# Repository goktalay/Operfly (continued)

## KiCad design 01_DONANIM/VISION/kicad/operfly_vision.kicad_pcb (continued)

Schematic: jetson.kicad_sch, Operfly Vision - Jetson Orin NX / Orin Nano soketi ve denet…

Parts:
C51: 1n; C_0402_1005Metric
C52, C53, C54, C55, C56, C57, C58, C59, C60, C61, C62, C63: 220n; C_0402_1005Metric
J2: Jetson Orin NX / Orin Nano; SODIMM-260_DDR4_H4.0-5.2_OrientationStd_Socket
Q2, Q3: 2N7002; SOT-23
R41: 1k; R_0402_1005Metric
R42, R45, R46, R47: 100k; R_0402_1005Metric
R43: 100k 1%; R_0402_1005Metric
R44: 33k 1%; R_0402_1005Metric
R48, R49: 0R; R_0402_1005Metric
TP7: JET_SYS_RESET_N; TestPoint_Pad_D1.0mm
TP8: JET_FRC_N; TestPoint_Pad_D1.0mm
TP9: JET_MOD_SLEEP_N; TestPoint_Pad_D1.0mm
TP10: JET_SLEEP_WAKE_N; TestPoint_Pad_D1.0mm
TP11: JET_DBG_TX; TestPoint_Pad_D1.0mm
TP12: JET_DBG_RX; TestPoint_Pad_D1.0mm

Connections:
+3V3: R45.1; also elsewhere on the board
+12V_JET: J2.251 (VDD_IN), J2.252 (VDD_IN), J2.253 (VDD_IN), J2.254 (VDD_IN), J2.255 (VDD_IN), J2.256 (VDD_IN), J2.257 (VDD_IN), J2.258 (VDD_IN), J2.259 (VDD_IN), J2.260 (VDD_IN); also elsewhere on the board
E1_CLKREQ_N: J2.182 (PCIE1_CLKREQ*), R48.1
E1_CLK_N: J2.173 (PCIE1_CLK_N); also elsewhere on the board
E1_CLK_P: J2.175 (PCIE1_CLK_P); also elsewhere on the board
E1_PER_N: C61.2; also elsewhere on the board
E1_PER_P: C60.2; also elsewhere on the board
E1_PET_C_N: J2.167 (PCIE1_RX0_N); also elsewhere on the board
E1_PET_C_P: J2.169 (PCIE1_RX0_P); also elsewhere on the board
E1_RST_N: J2.183 (PCIE1_RST*); also elsewhere on the board
E2_CLKREQ_N: J2.221 (PCIE2_CLKREQ*), R49.1
E2_CLK_N: J2.52 (PCIE2_CLK_N); also elsewhere on the board
E2_CLK_P: J2.54 (PCIE2_CLK_P); also elsewhere on the board
E2_PER_N: C63.2; also elsewhere on the board
E2_PER_P: C62.2; also elsewhere on the board
E2_PET_C_N: J2.40 (PCIE2_RX0_N); also elsewhere on the board
E2_PET_C_P: J2.42 (PCIE2_RX0_P); also elsewhere on the board
E2_RST_N: J2.219 (PCIE2_RST*); also elsewhere on the board
GND: C51.2, J2.1 (GND), J2.2 (GND), J2.7 (GND), J2.8 (GND), J2.13 (GND), J2.14 (GND), J2.19 (GND), J2.20 (GND), J2.25 (GND), J2.26 (GND), J2.31 (GND), J2.32 (GND), J2.37 (GND), J2.38 (GND), J2.43 (GND), J2.44 (GND), J2.49 (GND), J2.50 (GND), J2.55 (GND), J2.56 (GND), J2.61 (GND), J2.62 (GND), J2.67 (GND), J2.68 (GND), J2.73 (GND), J2.74 (GND), J2.79 (GND), J2.80 (GND), J2.85 (GND), J2.86 (GND), J2.102 (GND), J2.107 (GND), J2.113 (GND), J2.119 (GND), J2.125 (GND), J2.129 (GND), J2.132 (GND), J2.135 (GND), J2.138 (GND), J2.141 (GND), J2.144 (GND), J2.146 (GND), J2.147 (GND), J2.152 (GND), J2.153 (GND), J2.158 (GND), J2.159 (GND), J2.164 (GND), J2.165 (GND), J2.170 (GND), J2.171 (GND), J2.176 (GND), J2.177 (GND), J2.200 (GND), J2.201 (GND), J2.231 (GND), J2.241 (GND), J2.242 (GND), J2.243 (GND), J2.244 (GND), J2.245 (GND), J2.246 (GND), J2.247 (GND), J2.248 (GND), J2.249 (GND), J2.250 (GND), Q2.2 (S), Q3.2 (S), R42.2, R44.2, R46.2, R47.2, R48.2, R49.2; also elsewhere on the board
IMU_CS_N: J2.95 (SPI0_CS0*); also elsewhere on the board
IMU_INT: J2.211 (GPIO09); also elsewhere on the board
IMU_MISO: J2.93 (SPI0_MISO); also elsewhere on the board
IMU_MOSI: J2.89 (SPI0_MOSI); also elsewhere on the board
IMU_SCK: J2.91 (SPI0_SCK); also elsewhere on the board
JET_DBG_RX: J2.238 (UART2_RXD), TP12.1
JET_DBG_TX: J2.236 (UART2_TXD), TP11.1
JET_FAN_PWM_1V8: J2.230 (GPIO14); also elsewhere on the board
JET_FRC_N: J2.214 (FORCE_RECOVERY*), Q3.3 (D), TP8.1
JET_MODULE_ID: J2.217 (MODULE_ID), R45.2; also elsewhere on the board
JET_MOD_SLEEP_N: J2.178 (MOD_SLEEP*), TP9.1
JET_POWER_EN: R41.1, R42.1; also elsewhere on the board
JET_POWER_EN_R: J2.237 (POWER_EN), R41.2
JET_PPS_1V8: J2.206 (GPIO07); also elsewhere on the board
JET_RECOVERY: Q3.1 (G), R47.1; also elsewhere on the board
JET_RESET: Q2.1 (G), R46.1; also elsewhere on the board
JET_SHDN_REQ_12V: J2.233 (SHUTDOWN_REQ*), R43.1
JET_SHDN_REQ_N: C51.1, R43.2, R44.1; also elsewhere on the board
JET_SLEEP_WAKE_N: J2.240 (SLEEP/WAKE*), TP10.1
JET_SYS_RESET_N: J2.239 (SYS_RESET*), Q2.3 (D), TP7.1; also elsewhere on the board
JET_UART_RX_1V8: J2.205 (UART1_RXD); also elsewhere on the board
JET_UART_TX_1V8: J2.203 (UART1_TXD); also elsewhere on the board
JGBE_MDI0_N: J2.184 (GBE_MDI0_N); also elsewhere on the board
JGBE_MDI0_P: J2.186 (GBE_MDI0_P); also elsewhere on the board
JGBE_MDI1_N: J2.190 (GBE_MDI1_N); also elsewhere on the board
JGBE_MDI1_P: J2.192 (GBE_MDI1_P); also elsewhere on the board
JGBE_MDI2_N: J2.196 (GBE_MDI2_N); also elsewhere on the board
JGBE_MDI2_P: J2.198 (GBE_MDI2_P); also elsewhere on the board
JGBE_MDI3_N: J2.202 (GBE_MDI3_N); also elsewhere on the board
JGBE_MDI3_P: J2.204 (GBE_MDI3_P); also elsewhere on the board
J_PCIE0_TX0_N: C53.1, J2.134 (PCIE0_TX0_N)
J_PCIE0_TX0_P: C52.1, J2.136 (PCIE0_TX0_P)
J_PCIE0_TX1_N: C55.1, J2.140 (PCIE0_TX1_N)
J_PCIE0_TX1_P: C54.1, J2.142 (PCIE0_TX1_P)
J_PCIE0_TX2_N: C57.1, J2.148 (PCIE0_TX2_N)
J_PCIE0_TX2_P: C56.1, J2.150 (PCIE0_TX2_P)
J_PCIE0_TX3_N: C59.1, J2.154 (PCIE0_TX3_N)
J_PCIE0_TX3_P: C58.1, J2.156 (PCIE0_TX3_P)
J_PCIE1_TX_N: C61.1, J2.172 (PCIE1_TX0_N)
J_PCIE1_TX_P: C60.1, J2.174 (PCIE1_TX0_P)
J_PCIE2_TX_N: C63.1, J2.46 (PCIE2_TX0_N)
J_PCIE2_TX_P: C62.1, J2.48 (PCIE2_TX0_P)
M2_CLKREQ_N: J2.180 (PCIE0_CLKREQ*); also elsewhere on the board
M2_CLK_N: J2.160 (PCIE0_CLK_N); also elsewhere on the board
M2_CLK_P: J2.162 (PCIE0_CLK_P); also elsewhere on the board
M2_PER0_N: J2.131 (PCIE0_RX0_N); also elsewhere on the board
M2_PER0_P: J2.133 (PCIE0_RX0_P); also elsewhere on the board
M2_PER1_N: J2.137 (PCIE0_RX1_N); also elsewhere on the board
M2_PER1_P: J2.139 (PCIE0_RX1_P); also elsewhere on the board
M2_PER2_N: J2.149 (PCIE0_RX2_N); also elsewhere on the board
M2_PER2_P: J2.151 (PCIE0_RX2_P); also elsewhere on the board
M2_PER3_N: J2.155 (PCIE0_RX3_N); also elsewhere on the board
M2_PER3_P: J2.157 (PCIE0_RX3_P); also elsewhere on the board
M2_PET0_N: C53.2; also elsewhere on the board
M2_PET0_P: C52.2; also elsewhere on the board
M2_PET1_N: C55.2; also elsewhere on the board
M2_PET1_P: C54.2; also elsewhere on the board
M2_PET2_N: C57.2; also elsewhere on the board
M2_PET2_P: C56.2; also elsewhere on the board
M2_PET3_N: C59.2; also elsewhere on the board
M2_PET3_P: C58.2; also elsewhere on the board
M2_RST_N: J2.181 (PCIE0_RST*); also elsewhere on the board
PCIE_WAKE_N: J2.179 (PCIE_WAKE*); also elsewhere on the board
USB0_DM: J2.109 (USB0_D_N); also elsewhere on the board
USB0_DP: J2.111 (USB0_D_P); also elsewhere on the board
USB0_VBUS_DET_N: J2.87 (GPIO00); also elsewhere on the board

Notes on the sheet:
MODULE_ID: Orin'de bosta (100k ile 3,3 V'a cekilir = 1), yalniz 5 V'luk eski modulde GND.
Uc tablosu uretici veri sayfasindan (10_ORTAK_ARACLAR/kicad/jetson_uclari.py). Bos birakilan uclar bu kartta kullanilmaz.
JETSON SOKETI (260 uclu SO-DIMM). Birimler: guc ve denetim | PCIe, Ethernet, USB | dusuk hizli giris-cikislar | kullanilmayan goruntu uclari.
DENETIM: POWER_EN islemciden (1k seri; modulde 100k asagi cekme). SHUTDOWN_REQ* modulde 5k ile 12 V'a cekilidir -> 100k/33k ile islemciye.
PCIe: Jetson'in verici ciftlerinde 220 nF (alicilarin kondansatoru karsi taraftadir). Ethernet denetleyicilerinde saat istegi ucu yok:
SYS_RESET* ve FORCE_RECOVERY* 1,8 V hatlardir: islemci yalnizca transistorle DUSUGE ceker, hicbir zaman yuksege surmez.
PCIE1/PCIE2 CLKREQ* 0R ile GND'ye (saat surekli). Kondansatorler Jetson soketinin yanina konur.

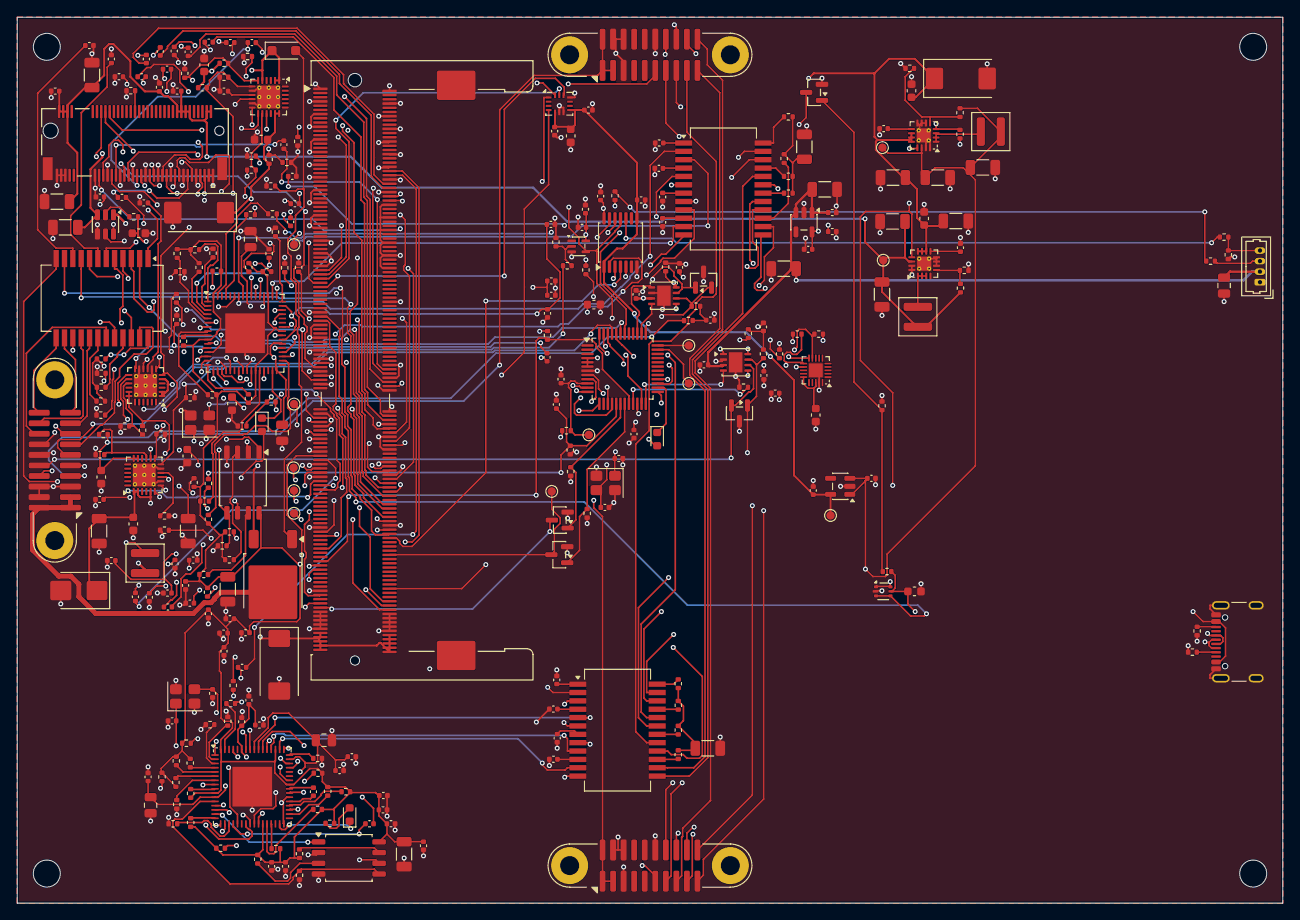
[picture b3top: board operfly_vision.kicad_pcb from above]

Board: 6 copper layers, 150.0 x 105.0 mm, 312 parts (0 on the bottom side), 300 nets.

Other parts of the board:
H1, H2, H3, H4: M3; MountingHole_3.2mm_M3

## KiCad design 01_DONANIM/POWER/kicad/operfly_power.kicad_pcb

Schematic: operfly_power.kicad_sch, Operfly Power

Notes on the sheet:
Operfly Power - guc karti (OPFPWR)
Sematik betikle uretilir: 01_DONANIM/POWER/kicad/uret.py.

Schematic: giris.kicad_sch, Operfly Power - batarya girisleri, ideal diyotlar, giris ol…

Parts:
C24, C26: 47n 100V; C_0603_1608Metric
C25, C27, C28, C29: 100n; C_0402_1005Metric
C30, C31: 100u 80V; CP_Elec_10x10.5
C32, C33: 2u2 100V; C_1210_3225Metric
D6, D8: SMAT70A; D_SMA
D7, D9: SMAJ24A; D_SMA
J2: Batarya A (XT60); AMASS_XT60-M_1x02_P7.20mm_Vertical
J3: Batarya B (XT60); AMASS_XT60-M_1x02_P7.20mm_Vertical
Q1, Q2: 100V lojik seviye, <=4 mR (secilecek); TDSON-8-1
R13, R16: 1k; R_0402_1005Metric
R14, R17: 200k 1%; R_0402_1005Metric
R15, R18: 10k 1%; R_0402_1005Metric
R19: 0R0005 1% 3W; R_Shunt_Isabellenhuette_BVR4026
R20, R21: 10R; R_0402_1005Metric
R22, R23: 2k2; R_0402_1005Metric
R24: 10k; R_0402_1005Metric
TP4: VIN; TestPoint_Pad_D1.0mm
U7, U8: LTC4359IDCB; DFN-6-1EP_3x2mm_P0.5mm_EP1.65x1.35mm
U9: INA228AIDGSR; TSSOP-10_3x3mm_P0.5mm

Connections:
+3V3: C29.1, R22.1, R23.1, R24.1, U9.6 (VS); also elsewhere on the board
BAT_A: D6.1 (K), J2.1, Q1.1 (S), Q1.2 (S), Q1.3 (S), R14.1, U7.3 (SRC), U7.4 (IN)
BAT_B: D8.1 (K), J3.1, Q2.1 (S), Q2.2 (S), Q2.3 (S), R17.1, U8.3 (SRC), U8.4 (IN)
GATE_A: Q1.4 (G), U7.2 (GATE)
GATE_B: Q2.4 (G), U8.2 (GATE)
GND: C24.2, C25.2, C26.2, C27.2, C29.2, C30.2, C31.2, C32.2, C33.2, D7.1 (K), D9.1 (K), J2.2, J3.2, R13.2, R15.2, R16.2, R18.2, U9.1 (A1), U9.2 (A0), U9.7 (GND); also elsewhere on the board
INA_INN: C28.2, R21.2, U9.9 (Vin-)
INA_INP: C28.1, R20.2, U9.10 (Vin+)
PWR_ALERT_N: R24.2, U9.3 (~Alert); also elsewhere on the board
PWR_SCL: R22.2, U9.5 (SCL); also elsewhere on the board
PWR_SDA: R23.2, U9.4 (SDA); also elsewhere on the board
SHUNT_N: R19.3, R21.1
SHUNT_P: R19.2, R20.1
TVS_A: D6.2 (A), D7.2 (A)
TVS_B: D8.2 (A), D9.2 (A)
VBAT_A_SENS: C25.1, R14.2, R15.1; also elsewhere on the board
VBAT_B_SENS: C27.1, R17.2, R18.1; also elsewhere on the board
VIN: C30.1, C31.1, C32.1, C33.1, R19.4, TP4.1, U9.8 (Vbus); also elsewhere on the board
VIN_OR: C24.1, C26.1, Q1.5 (D), Q2.5 (D), R19.1, U7.1 (OUT), U8.1 (OUT)
VSS_A: R13.1, U7.6 (Vss), U7.7 (Pad)
VSS_B: R16.1, U8.6 (Vss), U8.7 (Pad)

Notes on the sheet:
GIRIS OLCUMU (INA228): gerilim, akim ve harcanan enerji; I2C ile dugum islemcisine. Akim direnci 0,5 mR (30 A'de 0,45 W).
giriste iki kirpma diyotu (70 V ve ters yonde 24 V), VSS ucunda 1 k, cikista 47 nF. Ters baglanan batarya -40 V'a kadar zarar vermez.
BATARYA GIRISLERI (6-60 V): her giriste ideal diyot (LTC4359 + N kanal MOSFET). Devre ureticinin ornek devresidir:
VIN: olculmus, birlestirilmis giris gerilimi; 12 V ceviriciye ve servo rayina gider (bu sayfalar henuz cizilmedi).

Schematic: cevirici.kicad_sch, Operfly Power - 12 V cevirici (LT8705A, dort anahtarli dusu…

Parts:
C34, C40, C56: 100n; C_0402_1005Metric
C35: 1u; C_0603_1608Metric
C36: 10n; C_0402_1005Metric
C37: 220p; C_0402_1005Metric
C38, C39: 4u7 16V; C_0805_2012Metric
C41: 1u 100V; C_1206_3216Metric
C42, C43: 1n; C_0402_1005Metric
C44, C45: 220n 25V; C_0603_1608Metric
C46, C47, C48, C49: 2u2 100V; C_1210_3225Metric
C50, C51, C52, C53: 22u 25V; C_1210_3225Metric
C54, C55: 330u 25V; CP_Elec_8x10
D10, D11: ES1D (200 V, 1 A); D_SMA
F1: 2 A (kendini onaran); Fuse_1812_4532Metric
J4: 12 V cikis (XT60); AMASS_XT60-F_1x02_P7.20mm_Vertical
L2: 10u XAL1510-103; L_Coilcraft_XAL1510-103
Q3, Q4, Q5, Q6: FDMS86101; TDSON-8-1
Q7, Q8: BSC014N04LS; TDSON-8-1
R25: 215k 1%; R_0402_1005Metric
R26: 71k5 1%; R_0402_1005Metric
R27: 20k 1%; R_0402_1005Metric
R28: 100k 1%; R_0402_1005Metric
R29: 26k1 1%; R_0402_1005Metric
R30: 102k 1%; R_0402_1005Metric
R31: 11k3 1%; R_0402_1005Metric
R32: 33k2 1%; R_0402_1005Metric
R33: 16k5; R_0402_1005Metric
R34, R35: 10R; R_0402_1005Metric
R36, R37: 2R; R_0402_1005Metric
R38: 0R002 1% 3W; R_2512_6332Metric
R39: 0R004 1% 3W; R_2512_6332Metric
R40: 47k 1%; R_0402_1005Metric
R41: 10k 1%; R_0402_1005Metric
TP5: 12V_OUT; TestPoint_Pad_D1.0mm
U10: LT8705AIFE; Linear_HTSSOP-31-38-1EP_4.4x9.7mm_P0.5mm_EP2.74x4.75mm_Ther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

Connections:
12V_OUT: C50.1, C51.1, C52.1, C53.1, C54.1, C55.1, F1.1, J4.1, Q8.5 (D), R30.1, R40.1, TP5.1, U10.30 (EXTVCC), U10.32 (CSNOUT), U10.34 (CSPOUT)
+12V_BUS: F1.2; also elsewhere on the board
CV_BG1: Q5.4 (G), Q6.4 (G), U10.17 (BG1)
CV_BG2: Q7.4 (G), U10.19 (BG2)
CV_BOOST1: C44.1, D10.1 (K), U10.28 (BOOST1)
CV_BOOST2: C45.1, D11.1 (K), U10.20 (BOOST2)
CV_CSN: C43.1, R35.2, U10.5 (CSN)
CV_CSP: C42.1, R34.2, U10.6 (CSP)
CV_FBIN: R28.2, R29.1, U10.8 (FBIN)
CV_FBOUT: R30.2, R31.1, U10.9 (FBOUT)
CV_G1A: Q3.4 (G), R36.2
CV_G1B: Q4.4 (G), R37.2
CV_IMON_IN: C34.1, R32.1, U10.3 (IMON_IN)
CV_INTVCC: C38.1, C39.1, D10.2 (A), D11.2 (A), U10.1 (INTVCC), U10.18 (GATEVCC)
CV_LDO33: C40.1, U10.2 (MODE), U10.7 (LDO33)
CV_RS: Q5.1 (S), Q5.2 (S), Q5.3 (S), Q6.1 (S), Q6.2 (S), Q6.3 (S), Q7.1 (S), Q7.2 (S), Q7.3 (S), R34.1, R39.1
CV_RT: R25.1, U10.15 (RT)
CV_SHDN: R26.2, R27.1, U10.4 (~SHDN)
CV_SS: C35.1, U10.12 (SS)
CV_SW1: C44.2, L2.1, Q3.1 (S), Q3.2 (S), Q3.3 (S), Q4.1 (S), Q4.2 (S), Q4.3 (S), Q5.5 (D), Q6.5 (D), U10.24 (SW1)
CV_SW2: C45.2, L2.2, Q7.5 (D), Q8.1 (S), Q8.2 (S), Q8.3 (S), U10.22 (SW2)
CV_TG1: R36.1, R37.1, U10.26 (TG1)
CV_TG2: Q8.4 (G), U10.21 (TG2)
CV_VC: C37.1, R33.1, U10.11 (VC)
CV_VC_RC: C36.1, R33.2
GND: C34.2, C35.2, C36.2, C37.2, C38.2, C39.2, C40.2, C41.2, C42.2, C43.2, C46.2, C47.2, C48.2, C49.2, C50.2, C51.2, C52.2, C53.2, C54.2, C55.2, C56.2, J4.2, R25.2, R27.2, R29.2, R31.2, R32.2, R35.1, R39.2, R41.2, U10.10 (IMON_OUT), U10.14 (SYNC), U10.16 (GND), U10.39 (GND); also elsewhere on the board
V12_SENS: C56.1, R40.2, R41.1; also elsewhere on the board
VIN: R38.1, U10.37 (CSPIN); also elsewhere on the board
VIN_SW: C41.1, C46.1, C47.1, C48.1, C49.1, Q3.5 (D), Q4.5 (D), R26.1, R28.1, R38.2, U10.36 (CSNIN), U10.38 (VIN)

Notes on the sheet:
AYAR ve DESTEK ELEMANLARI
GUC KATI: giris tarafi 100 V, 8 mR MOSFET (ikiser adet); cikis tarafi 40 V, 1,4 mR MOSFET (aday). Hepsi 6 V kapi geriliminde tam acilan tipte olmali.
202 kHz, bobin 10 uH, akim direnci 4 mR, giris akim siniri 18 A (10 V altinda guc kendiliginden azalir).
CIKIS: 12 V ana cikis XT60 ile Hub'a gider (150 W omurga fisinden gecmez). Omurga fisi 2 A sigortayla beslenir; dugum buradan calisir.
ILK TASLAK: kompanzasyon ve isil hesap benzetimle (LTspice) dogrulanmadan uretime gonderilmez.
12 V CEVIRICI: ureticinin '12 V cikis, 4-80 V giris' ornek devresi 5 A'den 12,5 A'e olceklendi (150 W).

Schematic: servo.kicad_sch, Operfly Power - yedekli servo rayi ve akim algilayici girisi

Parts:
C57, C58, C68, C69: 2u2 100V; C_1210_3225Metric
C59, C70: 100n 100V; C_0603_1608Metric
C60, C71: 6n8; C_0402_1005Metric
C61, C72: 47p; C_0402_1005Metric
C62, C73: 100n 25V; C_0603_1608Metric
C63, C64, C65, C74, C75, C76, C79, C80: 47u 16V; C_1210_3225Metric
C66, C77, C81, C82: 100n; C_0402_1005Metric
C67, C78: 47n 25V; C_0402_1005Metric
D12, D13: PDS760 (60 V, 7 A); D_PowerDI-5
J5: Servo rayi (XT30); AMASS_XT30U-M_1x02_P5.0mm_Vertical
J6: Akim algilayici; JST_GH_SM03B-GHS-TB_1x03-1MP_P1.25mm_Horizontal
L3, L4: 10u XAL7070-103; L_Coilcraft_XAL7070-XXX
Q9, Q11: 2N7002; SOT-23
Q10, Q12: BSC014N04LS; TDSON-8-1
R42, R50: 243k 1%; R_0402_1005Metric
R43, R51: 16k5; R_0402_1005Metric
R44, R52: 66k5 1%; R_0402_1005Metric
R45, R53: 10k2 1%; R_0402_1005Metric
R46, R54, R58: 30k 1%; R_0402_1005Metric
R47, R55, R59, R60: 10k 1%; R_0402_1005Metric
R48, R56: 100k; R_0402_1005Metric
R49, R57: 1k; R_0402_1005Metric
R61: 20k 1%; R_0402_1005Metric
TP6: SERVO_V; TestPoint_Pad_D1.0mm
U11, U13: TPS54560BDDAR; Texas_R-PDSO-G8_EP2.95x4.9mm_Mask2.4x3.1mm_ThermalVias
U12, U14: LTC4359IDCB; DFN-6-1EP_3x2mm_P0.5mm_EP1.65x1.35mm

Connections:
+5V: J6.1; also elsewhere on the board
GND: C57.2, C58.2, C59.2, C60.2, C61.2, C63.2, C64.2, C65.2, C66.2, C67.2, C68.2, C69.2, C70.2, C71.2, C72.2, C74.2, C75.2, C76.2, C77.2, C78.2, C79.2, C80.2, C81.2, C82.2, D12.2 (A), D13.2 (A), J5.2, J6.3, Q9.2 (S), Q11.2 (S), R42.2, R45.2, R47.2, R48.2, R49.2, R50.2, R53.2, R55.2, R56.2, R57.2, R59.2, R61.2, U11.7 (GND), U11.9 (GND), U13.7 (GND), U13.9 (GND); also elsewhere on the board
IBAT_RAW: J6.2, R60.1
IBAT_SENS: C82.1, R60.2, R61.1; also elsewhere on the board
SERVO_SENS: C81.1, R58.2, R59.1; also elsewhere on the board
SERVO_V: C67.1, C78.1, C79.1, C80.1, J5.1, Q10.5 (D), Q12.5 (D), R58.1, TP6.1, U12.1 (OUT), U14.1 (OUT)
SRV_A: C63.1, C64.1, C65.1, L3.2, Q10.1 (S), Q10.2 (S), Q10.3 (S), R44.1, R46.1, U12.3 (SRC), U12.4 (IN)
SRV_A_BOOT: C62.1, U11.1 (BOOT)
SRV_A_COMP: C61.1, R43.1, U11.6 (COMP)
SRV_A_COMP_RC: C60.1, R43.2
SRV_A_EN: Q9.3 (D), U11.3 (EN)
SRV_A_FB: R44.2, R45.1, U11.5 (FB)
SRV_A_GATE: Q10.4 (G), U12.2 (GATE)
SRV_A_OFF: Q9.1 (G), R48.1; also elsewhere on the board
SRV_A_RT: R42.1, U11.4 (RT/CLK)
SRV_A_SENS: C66.1, R46.2, R47.1; also elsewhere on the board
SRV_A_SW: C62.2, D12.1 (K), L3.1, U11.8 (SW)
SRV_A_VSS: R49.1, U12.6 (Vss), U12.7 (Pad)
SRV_B: C74.1, C75.1, C76.1, L4.2, Q12.1 (S), Q12.2 (S), Q12.3 (S), R52.1, R54.1, U14.3 (SRC), U14.4 (IN)
SRV_B_BOOT: C73.1, U13.1 (BOOT)
SRV_B_COMP: C72.1, R51.1, U13.6 (COMP)
SRV_B_COMP_RC: C71.1, R51.2
SRV_B_EN: Q11.3 (D), U13.3 (EN)
SRV_B_FB: R52.2, R53.1, U13.5 (FB)
SRV_B_GATE: Q12.4 (G), U14.2 (GATE)
SRV_B_OFF: Q11.1 (G), R56.1; also elsewhere on the board
SRV_B_RT: R50.1, U13.4 (RT/CLK)
SRV_B_SENS: C77.1, R54.2, R55.1; also elsewhere on the board
SRV_B_SW: C73.2, D13.1 (K), L4.1, U13.8 (SW)
SRV_B_VSS: R57.1, U14.6 (Vss), U14.7 (Pad)
VIN: C57.1, C58.1, C59.1, C68.1, C69.1, C70.1, U11.2 (VIN), U13.2 (VIN); also elsewhere on the board

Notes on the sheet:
Cikis 6,0 V (66k5 / 10k2). Baska gerilim icin ust direnc: 5,0 V 53k6, 7,4 V 84k5, 8,4 V 97k6. Regulatorler varsayilan ACIK; islemci kapatabilir.
SERVO CIKISI (XT30) ve olcum; 400 A TEMASSIZ AKIM ALGILAYICI girisi (5 V beslemeli, analog cikisli harici algilayici; parca secilecek).
SERVO RAYI: iki bagimsiz regulator (TPS54560B, 60 V, 5 A, 400 kHz), cikislari ideal diyotla birlesir. Biri arizalanirsa digeri tasir.

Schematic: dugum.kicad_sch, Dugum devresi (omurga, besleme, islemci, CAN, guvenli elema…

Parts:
C1, C3: 10u 50V; C_1206_3216Metric
C2: 100n 50V; C_0603_1608Metric
C4, C10, C11, C12, C15, C16, C17, C19, C20, C22: 100n; C_0402_1005Metric
C5, C6: 22u 16V; C_1206_3216Metric
C7, C8: 1u; C_0402_1005Metric
C9: 4u7; C_0603_1608Metric
C13, C14: 10p; C_0402_1005Metric
C18, C21: 4n7 DNP; C_0402_1005Metric; not fitted
C23: 2u2; C_0603_1608Metric
D1: B360A (60 V, 3 A); D_SMA
D2: SMBJ18A; D_SMB
D3: LED yesil; LED_0603_1608Metric
D4, D5: NUP2105L; SOT-23
J1: Operfly Bus; Harwin_Gecko_G125-MS12005M2P_2x10_P1.25mm_Vertical
L1: 4u7 XAL4020-472; L_Coilcraft_XAL4020-XXX
R1: 100k; R_0402_1005Metric
R2, R4, R7, R12: 10k; R_0402_1005Metric
R3: 1k; R_0402_1005Metric
R5, R6, R8, R9: 60R4 DNP; R_0402_1005Metric; not fitted
R10, R11: 2k2; R_0402_1005Metric
TP1: SWDIO; TestPoint_Pad_D1.0mm
TP2: SWCLK; TestPoint_Pad_D1.0mm
TP3: NRST; TestPoint_Pad_D1.0mm
U1: AP63205QWU; TSOT-23-6
U2: LP5907MFX-3.3; SOT-23-5
U3: STM32G0B1CET6; LQFP-48_7x7mm_P0.5mm
U4, U5: TJA1051TK/3; HVSON-8-1EP_3x3mm_P0.65mm_EP1.6x2.4mm
U6: SE050E2HQ1; QFN-20-1EP_3x3mm_P0.4mm_EP1.65x1.65mm
Y1: 16 MHz; Crystal_SMD_3225-4Pin_3.2x2.5mm

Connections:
+3V3: C8.1, C9.1, C10.1, C11.1, C12.1, C17.1, C20.1, C22.1, R2.1, R3.1, R10.1, R11.1, R12.1, U2.5 (OUT), U3.4 (VBAT), U3.5 (VREF+), U3.6 (VDD), U4.5 (VIO), U5.5 (VIO), U6.12 (VIN); also elsewhere on the board
+5V: C5.1, C6.1, C7.1, C16.1, C19.1, L1.2, U1.1 (FB), U2.1 (IN), U2.3 (EN), U4.3 (VCC), U5.3 (VCC); also elsewhere on the board
+12V: C1.1, C2.1, C3.1, D1.1 (K), D2.1 (A1), R1.1, U1.3 (IN)
+12V_BUS: D1.2 (A), J1.1 (+12V), J1.2 (+12V), J1.11 (+12V); also elsewhere on the board
BST_5V: C4.1, U1.6 (BST)
CAN_A_H: D4.1 (K), J1.4 (CAN_A_H), R5.1, U4.7 (CANH)
CAN_A_L: D4.2 (K), J1.14 (CAN_A_L), R6.1, U4.6 (CANL)
CAN_A_RX: U3.38 (PD0), U4.4 (RXD)
CAN_A_S: R4.1, U3.27 (PB15), U4.8 (S)
CAN_A_TERM: C18.1, R5.2, R6.2
CAN_A_TX: U3.39 (PD1), U4.1 (TXD)
CAN_B_H: D5.1 (K), J1.5 (CAN_B_H), R8.1, U5.7 (CANH)
CAN_B_L: D5.2 (K), J1.15 (CAN_B_L), R9.1, U5.6 (CANL)
CAN_B_RX: U3.24 (PB12), U5.4 (RXD)
CAN_B_S: R7.1, U3.21 (PB2), U5.8 (S)
CAN_B_TERM: C21.1, R8.2, R9.2
CAN_B_TX: U3.25 (PB13), U5.1 (TXD)
EN_5V: R1.2, U1.2 (EN)
GND: C1.2, C2.2, C3.2, C5.2, C6.2, C7.2, C8.2, C9.2, C10.2, C11.2, C12.2, C13.2, C14.2, C15.2, C16.2, C17.2, C18.2, C19.2, C20.2, C21.2, C22.2, C23.2, D2.2 (A2), D4.3 (A), D5.3 (A), J1.3 (GND), J1.12 (GND), J1.13 (GND), J1.16 (GND), R4.2, R7.2, U1.4 (GND), U2.2 (GND), U3.7 (VSS), U4.2 (GND), U4.9 (GND), U5.2 (GND), U5.9 (GND), U6.19 (VSS), U6.21 (EP), Y1.2 (G), Y1.4 (G); also elsewhere on the board
HSE_IN: C13.1, U3.8 (PF0), Y1.1
HSE_OUT: C14.1, U3.9 (PF1), Y1.3
IBAT_SENS: U3.17 (PA6); also elsewhere on the board
LED_DURUM: D3.1 (K), U3.26 (PB14)
LED_DURUM_A: D3.2 (A), R3.2
NRST: C15.1, R2.2, TP3.1, U3.10 (PF2)
PWR_ALERT_N: U3.42 (PB3); also elsewhere on the board
PWR_SCL: U3.22 (PB10); also elsewhere on the board
PWR_SDA: U3.23 (PB11); also elsewhere on the board
SERVO_SENS: U3.14 (PA3); also elsewhere on the board
SE_ENA: R12.2, U3.44 (PB5), U6.11 (ENA)
SE_SCL: R10.2, U3.47 (PB8), U6.10 (I2C_SCL)
SE_SDA: R11.2, U3.48 (PB9), U6.9 (I2C_SDA)
SE_VCC: C23.1, U6.15 (VOUT), U6.18 (VCC)
SRV_A_OFF: U3.45 (PB6); also elsewhere on the board
SRV_A_SENS: U3.15 (PA4); also elsewhere on the board
SRV_B_OFF: U3.46 (PB7); also elsewhere on the board
SRV_B_SENS: U3.16 (PA5); also elsewhere on the board
SWCLK: TP2.1, U3.36 (PA14)
SWDIO: TP1.1, U3.35 (PA13)
SW_5V: C4.2, L1.1, U1.5 (SW)
V12_SENS: U3.13 (PA2); also elsewhere on the board
VBAT_A_SENS: U3.11 (PA0); also elsewhere on the board
VBAT_B_SENS: U3.12 (PA1); also elsewhere on the board

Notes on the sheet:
DUGUM ISLEMCISI (STM32G0B1CET6): omurgaya iki CAN FD hattiyla baglanir, kimligini guvenli elemanla kanitlar.
OMURGA PORTU ve GIRIS KORUMASI: ters baglanti diyotu, 18 V kirpma diyotu. +12V korumali omurga gerilimidir.
GUVENLI ELEMAN (SE050): kart kimligi ve sertifikasi. SE_ENA sifira cekilince eleman kapanir (sifirlama).
BESLEME: 12 V -> 5 V (AP63205, 2 A) -> 3,3 V (LP5907, 250 mA). 3,3 V'ta daha fazla akim isteyen kart kendi regulatorunu ekler.
CAN FD: iki bagimsiz alici-verici (TJA1051-3). Sessiz mod girisi asagi cekili. Sonlandirma Hub'dadir; yerleri hazir, dizilmez.

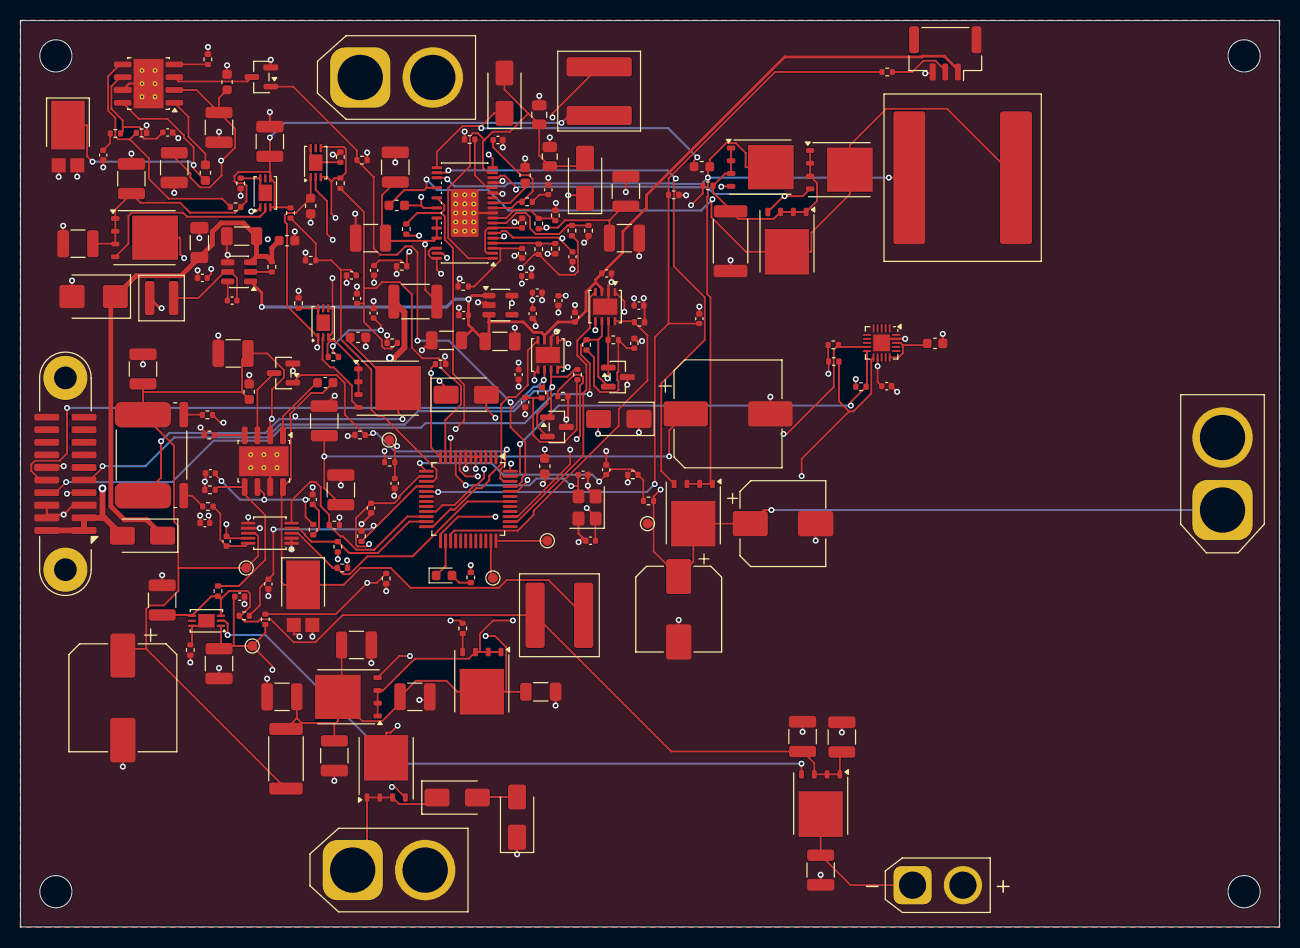
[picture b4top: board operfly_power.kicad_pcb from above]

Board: 4 copper layers, 125.0 x 90.0 mm, 204 parts (0 on the bottom side), 104 nets.

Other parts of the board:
H1, H2, H3, H4: M3; MountingHole_3.2mm_M3

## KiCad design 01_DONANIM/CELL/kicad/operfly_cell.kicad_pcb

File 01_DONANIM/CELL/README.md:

# Operfly Cell (OPFCEL)

5G hücresel bağlantı kartı: telemetri ve görüntü için ikinci haberleşme yolu. Kart hazır bir M.2 5G modemi taşır,
besler ve onu omurganın Ethernet'ine bağlar.

## Durum (15 Kasım 2026)

- KiCad projesi: `kicad/operfly_cell.kicad_pro`.
  Üretim ve denetim: `python 10_ORTAK_ARACLAR/kicad/denetle.py CELL operfly_cell`.
- Şematik tamam, 4 sayfa: kök, düğüm (`dugum`), modem (`modem`), Ethernet (`ethernet`). ERC 0 hata, 0 uyarı.
  Kart çizimi başlamadı.

## Kararlar (sahibi kararı tasarımcıya bıraktı)

1. **Modem hazır M.2 modüldür; aday Quectel RM520N-GL** (M.2 Key B, 30 × 52 mm). 5G'nin n28 ve n78 bantlarını
   (Türkiye) ve 4G'yi destekler; 5G yoksa 4G'ye düşer. Uç sıraları üreticinin donanım tasarım kılavuzundan alındı
   (RM520N-GL Hardware Design V1.0, Tablo 5).
2. **Veri yolu: modem → PCIe → karttaki Ethernet denetleyici → omurga Ethernet'i.** Modem PCIe'yi "kök" kipinde
   çalıştırır ve karttaki gigabit Ethernet denetleyiciyi (Realtek RTL8111H) kendisi sürer; kart omurgaya sıradan bir
   Ethernet cihazı olarak çıkar. Gerekçe: düğüm işlemcisi (USB tam hız, 12 Mbit) görüntü trafiğini taşıyamaz;
   omurganın yüksek hızlı yolu Ethernet'tir. Piyasadaki "5G modem → Ethernet" kartları da aynı yapıyı kullanır.
3. **Düğüm işlemcisi veri taşımaz, modemi yönetir:** beslemeyi açar/kapatır, modemi kurallı biçimde kapatır,
   sıfırlar, uçak kipine alır; USB üzerinden AT komutlarıyla sinyal gücünü, şebeke kaydını ve SIM seçimini okur ve
   omurgadan (CAN FD) bildirir. Böylece 5G bağlantısının durumu uçuş bilgisayarına Ethernet'ten bağımsız ulaşır.
4. **Modemin USB'si bir anahtarla (FSUSB42) iki yere verilir:** kablo takılı değilken düğüm işlemcisine, servis
   USB'sine (Type-C) kablo takılınca bilgisayara. Modem yazılımı yalnızca USB'den güncellenebildiği için servis
   portu zorunludur.
5. **Modem beslemesi ayrı regülatördür: 3,8 V / 5 A (TPS54560B, omurga 12 V'undan).** Modem 3,135–4,4 V ister ve
   verici patlamalarında 3 A çeker; üretici en az 3 A sürekli akım, 2 × 220 µF düşük ESR kondansatör, seramik dizi
   ve 5 V kırpma diyodu ister (hepsi kartta). Regülatör Power kartındaki servo regülatörüyle aynı parçadır.
6. **Giriş alt gerilim kilidi:** regülatör 9,0 V'ta açar, 8,0 V'ta kapatır (omurga çökerken modem açılıp kapanmaz).
7. **Ethernet denetleyicinin 3,3 V'u ayrıdır (TPS62130, 5 V'tan)** ve modem beslemesi gelince açar. Modem
   beslemesi yokken denetleyici ve PCIe yukarı çekme dirençleri de gerilimsiz kalır; kapalı modemin uçlarına
   gerilim verilmez.
8. **İki nano-SIM yuvası (çift operatör).** Modem aynı anda birini kullanır; diğerine AT komutuyla geçilir.
   Kart algılama (sıcak takma) kullanılmaz. İkinci yuvanın hatlarında üreticinin önerdiği 0 Ω dirençler var: dahili
   eSIM'li modem sürümü takılırsa bu dirençler dizilmez.
9. **Lehimli eSIM bu revizyonda yok.** Lehimli eSIM yongasının uç sırası burada doğrulanamadı ve operatör profili
   sözleşmesi gerektirir; ikinci nano-SIM yuvası aynı işi görür (nano-SIM biçiminde eSIM kartları da takılabilir).
10. **Antenler modülün kendi konnektörlerinden çıkar** (4 adet, ince koaksiyel kabloyla kasadaki SMA'lara). Kartta
    RF izi yoktur; kartın RF tasarımı ve ölçümü gerekmez.
11. **Modemin konum alıcısı kullanılmaz;** konum Nav kartından gelir.

## Sahibinin bilmesi gerekenler

- **Modem ayrı satın alınır** ve yuvaya takılır; SIM kartlar (ya da eSIM profili) operatörden alınır.
- **İlk kurulumda modem bir kez ayarlanır** (servis USB'sinden ya da düğüm işlemcisinden AT komutlarıyla): PCIe kök
  kipi ve Ethernet denetleyici sürücüsü açılır. Bu ayarlar modemde kalıcıdır; üretimde otomatikleştirilecek.
- **Servis USB'si kartı beslemez.** Modem ayarlanırken ya da güncellenirken kart omurgadan beslenmelidir.
- **Besleme modem kapatılmadan kesilmemelidir.** Üretici, modem kapatma ucuyla kapatılıp yaklaşık 1 s beklenmeden
  beslemenin kesilmesinin modemin belleğini bozabileceğini yazar. Düğüm yazılımı bunu sırayla yapar; uçakta ana
  şalter aniden kapatılırsa bu kural çiğnenir (aşağıda "Doğrulanacaklar").
- **Modem ısınır;** üretici çalışma sıcaklığı aralığı (−30…+75 °C) için soğutma ister. Kasada modemin altına ısı
  dolgusu ve soğutucu gerekir.
- **Güç:** tepe yaklaşık 11 W (12 V'ta 1 A), ortalama birkaç watt. Hub portunun 6 A sınırı içinde.
- **Havada 5G/4G kapsaması yerdeki gibi değildir:** baz istasyonu antenleri yere bakar; yükseldikçe bağlantı
  bozulabilir ve bir cihazın havadan şebekeyi kullanması operatör koşullarına bağlıdır. Cell bu yüzden *ikinci*
  haberleşme yoludur, birincisi değil.
- **Trafik şifreli tünelden geçer** (kartın sertifikasıyla); bu yazılım işidir, donanımda ek parça gerektirmez.

## Doğrulanacaklar

- **Modemin Ethernet denetleyici desteği yazılım sürümüne bağlıdır.** PCIe kök kipi üreticinin kılavuzunda var
  (uç tablosu dipnotu ve AT komutu); RTL8111H sürücüsünün modem yazılımında bulunduğu ise yalnızca kullanıcı
  forumlarından biliniyor. Numune modemle denenecek; gerekirse üreticiden doğru yazılım sürümü istenecek.
  Olmazsa aynı ayak izi ailesinden RTL8125B'ye geçiş (2,5 Gbit) değerlendirilecek.
- **Ethernet denetleyicinin çevre değerleri** (RSET 2,49 kΩ, 1,0 V çıkış kondansatörleri, ISOLATEB bölücüsü, LED
  uçları, kristal yük kondansatörleri) üreticinin başvuru şematiğinden değil, aynı ailenin yaygın uygulamalarından
  alındı; veri sayfası bu değerleri vermiyor. Realtek başvuru şematiğiyle karşılaştırılacak.
- **Ethernet denetleyicinin MAC adresi** entegrenin bir kez yazılır belleğinde durur; boş entegrede adresin nasıl
  atanacağı (üretimde yazma ya da modem tarafında atama) netleşecek.
- **Ayak izleri:** RTL8111H alt ped ölçüsü ve M.2 yuvasının yüksekliği/vida yeri (30 × 52 mm modül) üretici
  çizimleriyle doğrulanacak.
- **Regülatör kompanzasyonu** (26,7 kΩ, 15 nF, 220 pF) veri sayfasındaki formüllerle hesaplandı; üreticinin tasarım
  aracıyla ve yük adımı ölçümüyle doğrulanacak. Modem patlamalarında gerilim düşüşü ve dalgalanma (< 100 mV) ölçülecek.
- **Ani besleme kesilmesi:** modemin kurallı kapanması için 1 s'lik enerji deposu (süper kondansatör) gerekip
  gerekmediği numunede denenecek.
- **Düğüm işlemcisinin USB ana bilgisayar kipi:** aşağı çekme dirençlerinin işlemcinin içinde olduğu varsayıldı;
  kartta dizilmeyen 15 kΩ yerleri bırakıldı. Modemin tam hızda (12 Mbit) tanınması numunede denenecek.
- **Cihaz kaydı ve operatör uyumluluğu:** modülün Türkiye'de kullanım onayı, IMEI kaydı, operatörlerin bant ve
  hizmet (havadan kullanım, sabit IP/APN) koşulları teyit edilecek.
- **Şifreleme için ihracat/ithalat koşulları** ve modülün menşe/ihracat sınıfı teyit edilecek.
- **Çalışma sıcaklığı:** modül −40 °C'ye kadar "genişletilmiş" aralıkta çalışır ama başarımı garanti etmez; askeri
  sıcaklık aralığı hedefi için değerlendirilecek.

## Kart çizimi (otomatik)

Sahibinin kararıyla kart **otomatik** çizildi: yerleşim `pcb_yerlesim.py`, yollar dış bir otomatik yol çiziciyle
(`pcb_ciz.py`). Dosya: `kicad/operfly_cell.kicad_pcb`; ayarlar `kicad/pcb_ayar.py`.
Yeniden üretmek için: `python 10_ORTAK_ARACLAR/kicad/pcb_ciz.py CELL operfly_cell`.

- **Kart:** 110 x 85 mm, 6 katman (iç 1: toprak, iç 4: +3V3; diğer katmanlar sinyal, elemanlar üstte), 182 eleman, tamamı üst yüzde; köşelerde M3 montaj deliği.
- **Kurallar:** yol 0,20 mm, açıklık 0,125 mm, geçiş 0,6/0,3 mm; besleme ağları, ağın en dar ucunu aşmayacak biçimde 0,2-1,0 mm (0,4 mm ve üstünde geçiş 0,8/0,4 mm); bakır-kenar 0,25 mm.
- **Denetim:** DRC 0 ihlal, 0 bağlanmamış uç; şematik-kart uyumu temiz. 1775 yol parçası, 312 geçiş.

**Bu bir mühendis çizimi değildir.** Üretimden önce bir kart tasarımcısının bakması gereken noktalar:

- Yüksek hızlı fark çiftleri (PCIe, gigabit Ethernet, USB) 85/90/100 ohm empedansta, eşit uzunlukta ve kesintisiz toprak üstünde çizilmedi; bağlantı kurulamayabilir ya da hata verebilir. Bu çiftler elle yeniden çizilmeden kart işlevsel sayılmaz.
- M.2 yuvasının yönü (modemin girdiği yan) ve modemin kart üstünde yatacağı bölge üretici çizimiyle doğrulanmadı; modem sabitleme vidası için delik ve dayama yok.
- Modem beslemesi (3,8 V, verici darbelerinde 5 A'e kadar) dar yolla çizildi; yuva uçlarına geniş bakır ve yakın kondansatör gerekir.
- Modem yaklaşık 5-7 W ısı üretir; soğutma tasarlanmadı.
- Anahtarlamalı regülatörlerin (bobin, diyot, giriş/çıkış kondansatörleri) akım döngüleri küçük tutulmadı; gürültü ve verim ölçülmeli.
- Kristal ve osilatör hatları en kısa yoldan çizilmedi; altlarından başka sinyal geçip geçmediğine bakılmalı.
- Fark çiftleri (CAN, USB, Ethernet) çift olarak, eşit uzunlukta ve empedans denetimli çizilmedi.
- Güç elemanlarının soğutma bakırı ve ısıl geçişleri ayrıca hesaplanmadı.
- Eleman adları üretim katmanında bırakıldı; kart üstünde yazı (serigrafi) yok.
- Kasa, konnektör yerleri ve montaj delikleri mekanik tasarımla eşleştirilmedi.
- Üretim dosyaları (Gerber, delik, dizgi) henüz çıkarılmadı.

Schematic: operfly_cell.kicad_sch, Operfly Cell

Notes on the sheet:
Operfly Cell - 5G hucresel baglanti karti (OPFCEL)
Sematik betikle uretilir: 01_DONANIM/CELL/kicad/uret.py. Modem M.2 yuvasina takilir; anten kablolari modulun kendi konnektorlerinden cikar.

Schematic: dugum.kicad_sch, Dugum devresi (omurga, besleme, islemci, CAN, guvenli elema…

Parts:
C1, C3: 10u 50V; C_1206_3216Metric
C2: 100n 50V; C_0603_1608Metric
C4, C10, C11, C12, C15, C16, C17, C19, C20, C22: 100n; C_0402_1005Metric
C5, C6: 22u 16V; C_1206_3216Metric
C7, C8: 1u; C_0402_1005Metric
C9: 4u7; C_0603_1608Metric
C13, C14: 10p; C_0402_1005Metric
C18, C21: 4n7 DNP; C_0402_1005Metric; not fitted
C23: 2u2; C_0603_1608Metric
D1: B360A (60 V, 3 A); D_SMA
D2: SMBJ18A; D_SMB
D3: LED yesil; LED_0603_1608Metric
D4, D5: NUP2105L; SOT-23
J1: Operfly Bus; Harwin_Gecko_G125-MS12005M2P_2x10_P1.25mm_Vertical
L1: 4u7 XAL4020-472; L_Coilcraft_XAL4020-XXX
R1: 100k; R_0402_1005Metric
R2, R4, R7, R12: 10k; R_0402_1005Metric
R3: 1k; R_0402_1005Metric
R5, R6, R8, R9: 60R4 DNP; R_0402_1005Metric; not fitted
R10, R11: 2k2; R_0402_1005Metric
TP1: SWDIO; TestPoint_Pad_D1.0mm
TP2: SWCLK; TestPoint_Pad_D1.0mm
TP3: NRST; TestPoint_Pad_D1.0mm
U1: AP63205QWU; TSOT-23-6
U2: LP5907MFX-3.3; SOT-23-5
U3: STM32G0B1CET6; LQFP-48_7x7mm_P0.5mm
U4, U5: TJA1051TK/3; HVSON-8-1EP_3x3mm_P0.65mm_EP1.6x2.4mm
U6: SE050E2HQ1; QFN-20-1EP_3x3mm_P0.4mm_EP1.65x1.65mm
Y1: 16 MHz; Crystal_SMD_3225-4Pin_3.2x2.5mm

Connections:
+3V3: C8.1, C9.1, C10.1, C11.1, C12.1, C17.1, C20.1, C22.1, R2.1, R3.1, R10.1, R11.1, R12.1, U2.5 (OUT), U3.4 (VBAT), U3.5 (VREF+), U3.6 (VDD), U4.5 (VIO), U5.5 (VIO), U6.12 (VIN); also elsewhere on the board
+5V: C5.1, C6.1, C7.1, C16.1, C19.1, L1.2, U1.1 (FB), U2.1 (IN), U2.3 (EN), U4.3 (VCC), U5.3 (VCC); also elsewhere on the board
+12V: C1.1, C2.1, C3.1, D1.1 (K), D2.1 (A1), R1.1, U1.3 (IN); also elsewhere on the board
+12V_BUS: D1.2 (A), J1.1 (+12V), J1.2 (+12V), J1.11 (+12V)
BST_5V: C4.1, U1.6 (BST)
CAN_A_H: D4.1 (K), J1.4 (CAN_A_H), R5.1, U4.7 (CANH)
CAN_A_L: D4.2 (K), J1.14 (CAN_A_L), R6.1, U4.6 (CANL)
CAN_A_RX: U3.38 (PD0), U4.4 (RXD)
CAN_A_S: R4.1, U3.27 (PB15), U4.8 (S)
CAN_A_TERM: C18.1, R5.2, R6.2
CAN_A_TX: U3.39 (PD1), U4.1 (TXD)
CAN_B_H: D5.1 (K), J1.5 (CAN_B_H), R8.1, U5.7 (CANH)
CAN_B_L: D5.2 (K), J1.15 (CAN_B_L), R9.1, U5.6 (CANL)
CAN_B_RX: U3.24 (PB12), U5.4 (RXD)
CAN_B_S: R7.1, U3.21 (PB2), U5.8 (S)
CAN_B_TERM: C21.1, R8.2, R9.2
CAN_B_TX: U3.25 (PB13), U5.1 (TXD)
EN_5V: R1.2, U1.2 (EN)
ETH_A+: J1.7 (ETH_A+); also elsewhere on the board
ETH_A-: J1.17 (ETH_A-); also elsewhere on the board
ETH_B+: J1.8 (ETH_B+); also elsewhere on the board
ETH_B-: J1.18 (ETH_B-); also elsewhere on the board
ETH_C+: J1.9 (ETH_C+); also elsewhere on the board
ETH_C-: J1.19 (ETH_C-); also elsewhere on the board
ETH_D+: J1.10 (ETH_D+); also elsewhere on the board
ETH_D-: J1.20 (ETH_D-); also elsewhere on the board
ETH_PG: U3.42 (PB3); also elsewhere on the board
GND: C1.2, C2.2, C3.2, C5.2, C6.2, C7.2, C8.2, C9.2, C10.2, C11.2, C12.2, C13.2, C14.2, C15.2, C16.2, C17.2, C18.2, C19.2, C20.2, C21.2, C22.2, C23.2, D2.2 (A2), D4.3 (A), D5.3 (A), J1.3 (GND), J1.12 (GND), J1.13 (GND), J1.16 (GND), R4.2, R7.2, U1.4 (GND), U2.2 (GND), U3.7 (VSS), U4.2 (GND), U4.9 (GND), U5.2 (GND), U5.9 (GND), U6.19 (VSS), U6.21 (EP), Y1.2 (G), Y1.4 (G); also elsewhere on the board
HSE_IN: C13.1, U3.8 (PF0), Y1.1
HSE_OUT: C14.1, U3.9 (PF1), Y1.3
LED_DURUM: D3.1 (K), U3.26 (PB14)
LED_DURUM_A: D3.2 (A), R3.2
MCU_USB_DM: U3.33 (PA9/PA11); also elsewhere on the board
MCU_USB_DP: U3.34 (PA10/PA12); also elsewhere on the board
MODEM_ON: U3.16 (PA5); also elsewhere on the board
MODEM_PWR_OFF: U3.15 (PA4); also elsewhere on the board
MODEM_RF_EN: U3.18 (PA7); also elsewhere on the board
MODEM_RST: U3.17 (PA6); also elsewhere on the board
MODEM_VSENS: U3.11 (PA0); also elsewhere on the board
MODEM_WAKE_N: U3.19 (PB0); also elsewhere on the board
NRST: C15.1, R2.2, TP3.1, U3.10 (PF2)
SE_ENA: R12.2, U3.44 (PB5), U6.11 (ENA)
SE_SCL: R10.2, U3.47 (PB8), U6.10 (I2C_SCL)
SE_SDA: R11.2, U3.48 (PB9), U6.9 (I2C_SDA)
SE_VCC: C23.1, U6.15 (VOUT), U6.18 (VCC)
SWCLK: TP2.1, U3.36 (PA14)
SWDIO: TP1.1, U3.35 (PA13)
SW_5V: C4.2, L1.1, U1.5 (SW)
USB_SEL: U3.12 (PA1); also elsewhere on the board

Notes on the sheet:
OMURGA PORTU ve GIRIS KORUMASI: ters baglanti diyotu, 18 V kirpma diyotu. +12V korumali omurga gerilimidir.
DUGUM ISLEMCISI (STM32G0B1CET6): omurgaya iki CAN FD hattiyla baglanir, kimligini guvenli elemanla kanitlar.
BESLEME: 12 V -> 5 V (AP63205, 2 A) -> 3,3 V (LP5907, 250 mA). 3,3 V'ta daha fazla akim isteyen kart kendi regulatorunu ekler.
CAN FD: iki bagimsiz alici-verici (TJA1051-3). Sessiz mod girisi asagi cekili. Sonlandirma Hub'dadir; yerleri hazir, dizilmez.
GUVENLI ELEMAN (SE050): kart kimligi ve sertifikasi. SE_ENA sifira cekilince eleman kapanir (sifirlama).
